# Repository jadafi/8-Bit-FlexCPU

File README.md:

# 8-Bit-FlexCPU
Building Blocks for an 8-Bit CPU

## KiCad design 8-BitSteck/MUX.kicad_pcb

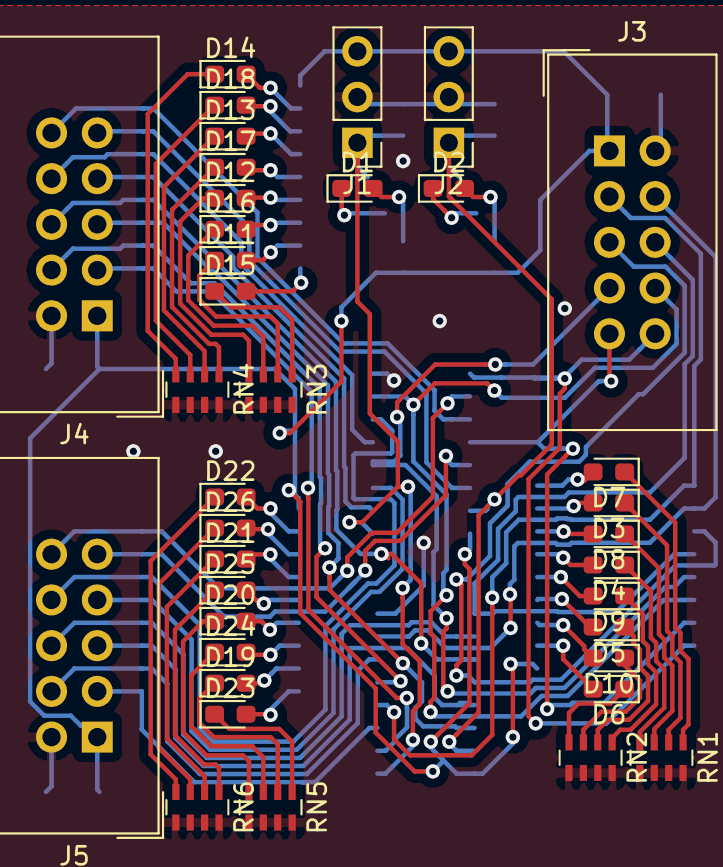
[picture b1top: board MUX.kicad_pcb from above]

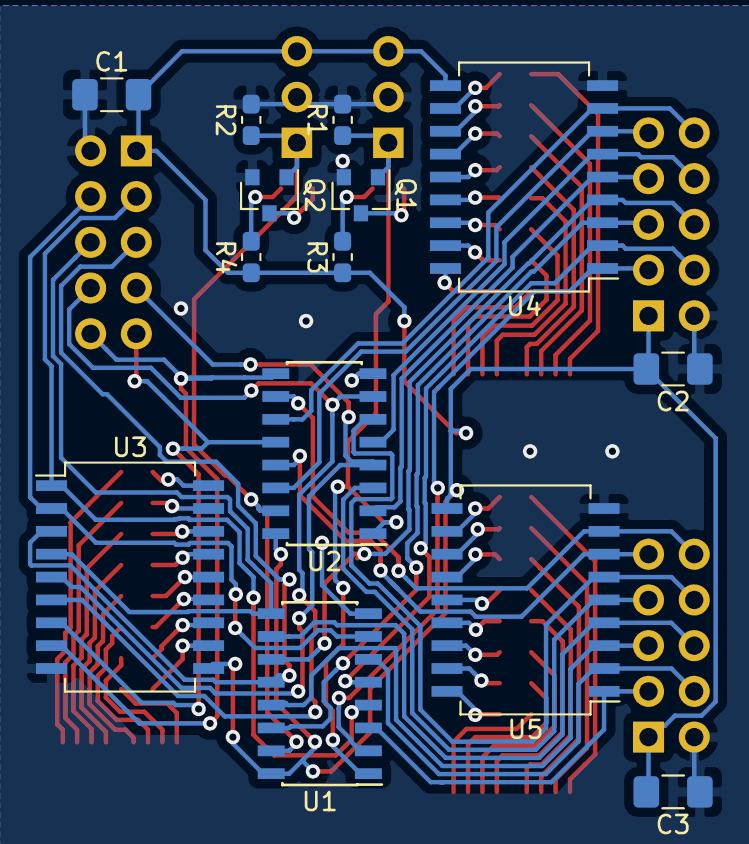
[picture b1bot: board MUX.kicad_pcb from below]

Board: 2 copper layers, 51 parts (14 on the bottom side), 80 nets.

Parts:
C1, C2, C3: _Decoupling; C_1206_3216Metric_Pad1.42x1.75mm_HandSolder
D1, D2: LED_Y; LED_0603_1608Metric_Pad1.05x0.95mm_HandSolder
D3, D4, D5, D6, D7, D8, D9, D10, D11, D12, D13, D14, D15, D16, D17, D18, D19, D20, D21, D22, D23, D24, D25, D26: LED; LED_0603_1608Metric_Pad1.05x0.95mm_HandSolder
J1, J2: Conn_01x03_Male; PinHeader_1x03_P2.54mm_Vertical
J3, J4, J5: Conn_02x05_Odd_Even; IDC-Header_2x05_P2.54mm_Vertical
Q1, Q2: 2N7002; SOT-23
R1, R2: R_default; R_0603_1608Metric_Pad1.05x0.95mm_HandSolder
R3, R4: R_Yellow; R_0603_1608Metric_Pad1.05x0.95mm_HandSolder
RN1, RN2, RN3, RN4, RN5, RN6: R_Pack04; R_Array_Concave_4x0603
U1, U2: 74LS157; SOIC-16_3.9x9.9mm_P1.27mm
U3, U4, U5: ULN2803A; SOP-18_7.0x12.5mm_P1.27mm

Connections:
+3V3: C1.2, C2.2, C3.2, J1.3, J2.3, J3.1, J4.1, J5.1, R3.1, R4.1, U1.16, U2.16, U3.10, U4.10, U5.10
/S: J1.1, Q1.1, R1.1, U1.1, U2.1
/a0: J4.3, U1.2, U4.1
/a1: J4.4, U1.5, U4.2
/a2: J4.5, U1.14, U4.3
/a3: J4.6, U1.11, U4.4
/a4: J4.7, U2.2, U4.5
/a5: J4.8, U2.5, U4.6
/a6: J4.9, U2.14, U4.7
/a7: J4.10, U2.11, U4.8
/b0: J5.3, U1.3, U5.1
/b1: J5.4, U1.6, U5.2
/b2: J5.5, U1.13, U5.3
/b3: J5.6, U1.10, U5.4
/b4: J5.7, U2.3, U5.5
/b5: J5.8, U2.6, U5.6
/b6: J5.9, U2.13, U5.7
/b7: J5.10, U2.10, U5.8
/out0: J3.3, U1.4, U3.1
/out1: J3.4, U1.7, U3.2
/out2: J3.5, U1.12, U3.3
/out3: J3.6, U1.9, U3.4
/out4: J3.7, U2.4, U3.5
/out5: J3.8, U2.7, U3.6
/out6: J3.9, U2.12, U3.7
/out7: J3.10, U2.9, U3.8
/~E: J2.1, Q2.1, R2.1, U1.15, U2.15
GND: C1.1, C2.1, C3.1, J1.2, J2.2, J3.2, J4.2, J5.2, Q1.2, Q2.2, R1.2, R2.2, RN1.5, RN1.6, RN1.7, RN1.8, RN2.5, RN2.6, RN2.7, RN2.8, RN3.5, RN3.6, RN3.7, RN3.8, RN4.5, RN4.6, RN4.7, RN4.8, RN5.5, RN5.6, RN5.7, RN5.8, RN6.5, RN6.6, RN6.7, RN6.8, U1.8, U2.8, U3.9, U4.9, U5.9
unnamed: D1.1, Q1.3
unnamed: D1.2, R3.2
unnamed: D2.1, Q2.3
unnamed: D2.2, R4.2
unnamed: D3.1, RN1.2
unnamed: D3.2, U3.17
unnamed: D4.1, RN1.4
unnamed: D4.2, U3.15
unnamed: D5.1, RN2.2
unnamed: D5.2, U3.13
unnamed: D6.1, RN2.4
unnamed: D6.2, U3.11
unnamed: D7.1, RN1.1
unnamed: D7.2, U3.18
unnamed: D8.1, RN1.3
unnamed: D8.2, U3.16
unnamed: D9.1, RN2.1
unnamed: D9.2, U3.14
unnamed: D10.1, RN2.3
unnamed: D10.2, U3.12
unnamed: D11.1, RN3.2
unnamed: D11.2, U4.17
unnamed: D12.1, RN3.4
unnamed: D12.2, U4.15
unnamed: D13.1, RN4.2
unnamed: D13.2, U4.13
unnamed: D14.1, RN4.4
unnamed: D14.2, U4.11
unnamed: D15.1, RN3.1
unnamed: D15.2, U4.18
unnamed: D16.1, RN3.3
unnamed: D16.2, U4.16
unnamed: D17.1, RN4.1
unnamed: D17.2, U4.14
unnamed: D18.1, RN4.3
unnamed: D18.2, U4.12
unnamed: D19.1, RN5.2
unnamed: D19.2, U5.17
unnamed: D20.1, RN5.4
unnamed: D20.2, U5.15
unnamed: D21.1, RN6.2
unnamed: D21.2, U5.13
unnamed: D22.1, RN6.4
unnamed: D22.2, U5.11
unnamed: D23.1, RN5.1
unnamed: D23.2, U5.18
unnamed: D24.1, RN5.3
unnamed: D24.2, U5.16
unnamed: D25.1, RN6.1
unnamed: D25.2, U5.14
unnamed: D26.1, RN6.3
unnamed: D26.2, U5.12

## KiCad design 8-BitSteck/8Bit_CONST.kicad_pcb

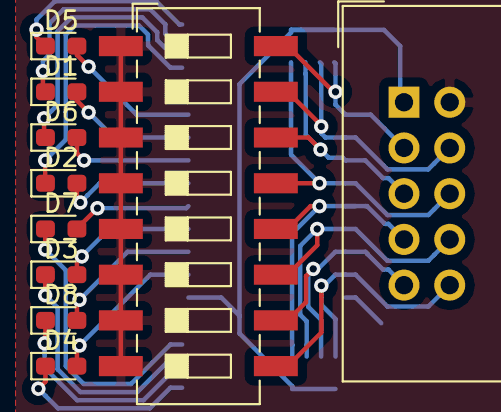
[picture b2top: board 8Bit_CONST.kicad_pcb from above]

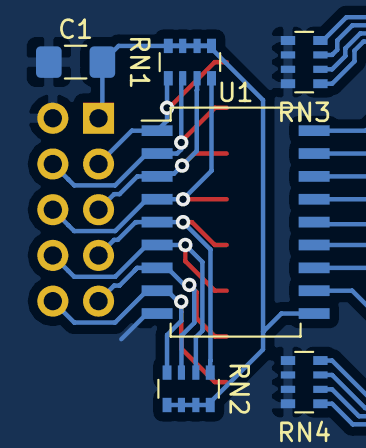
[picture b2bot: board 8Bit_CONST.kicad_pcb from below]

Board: 2 copper layers, 16 parts (6 on the bottom side), 26 nets.

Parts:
C1: _Decoupling; C_1206_3216Metric_Pad1.42x1.75mm_HandSolder
D1, D2, D3, D4, D5, D6, D7, D8: LED; LED_0603_1608Metric_Pad1.05x0.95mm_HandSolder
J1: Conn_02x05_Odd_Even; IDC-Header_2x05_P2.54mm_Vertical
RN1, RN2, RN3, RN4: R_Pack04; R_Array_Convex_4x0603
SW1: SW_DIP_x08; SW_DIP_SPSTx08_Slide_6.7x21.88mm_W8.61mm_P2.54mm_LowProfile
U1: ULN2803A; SOP-18_7.0x12.5mm_P1.27mm

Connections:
+3V3: C1.2, J1.1, RN1.5, RN1.6, RN1.7, RN1.8, RN2.5, RN2.6, RN2.7, RN2.8, U1.10
/bus0: J1.3, RN1.1, SW1.16, U1.1
/bus1: J1.4, RN1.2, SW1.15, U1.2
/bus2: J1.5, RN1.3, SW1.14, U1.3
/bus3: J1.6, RN1.4, SW1.13, U1.4
/bus4: J1.7, RN2.1, SW1.12, U1.5
/bus5: J1.8, RN2.2, SW1.11, U1.6
/bus6: J1.9, RN2.3, SW1.10, U1.7
/bus7: J1.10, RN2.4, SW1.9, U1.8
GND: C1.1, J1.2, RN3.5, RN3.6, RN3.7, RN3.8, RN4.5, RN4.6, RN4.7, RN4.8, SW1.1, SW1.2, SW1.3, SW1.4, SW1.5, SW1.6, SW1.7, SW1.8, U1.9
unnamed: D1.1, RN3.3
unnamed: D1.2, U1.17
unnamed: D2.1, RN3.1
unnamed: D2.2, U1.15
unnamed: D3.1, RN4.3
unnamed: D3.2, U1.13
unnamed: D4.1, RN4.1
unnamed: D4.2, U1.11
unnamed: D5.1, RN3.4
unnamed: D5.2, U1.18
unnamed: D6.1, RN3.2
unnamed: D6.2, U1.16
unnamed: D7.1, RN4.4
unnamed: D7.2, U1.14
unnamed: D8.1, RN4.2
unnamed: D8.2, U1.12

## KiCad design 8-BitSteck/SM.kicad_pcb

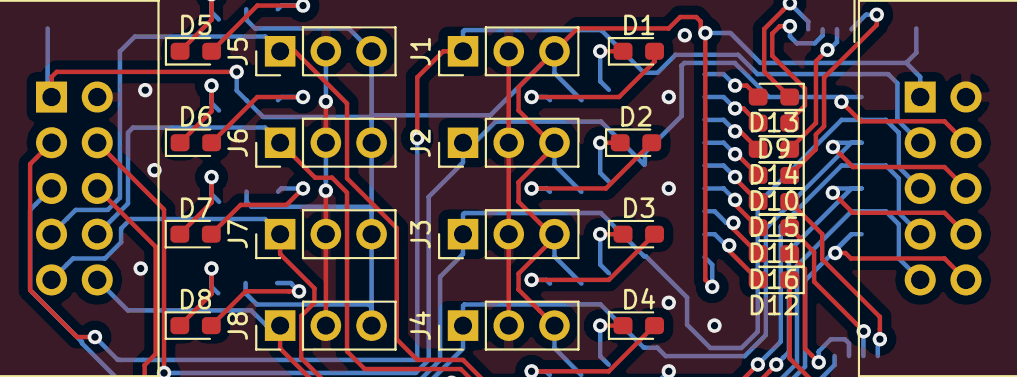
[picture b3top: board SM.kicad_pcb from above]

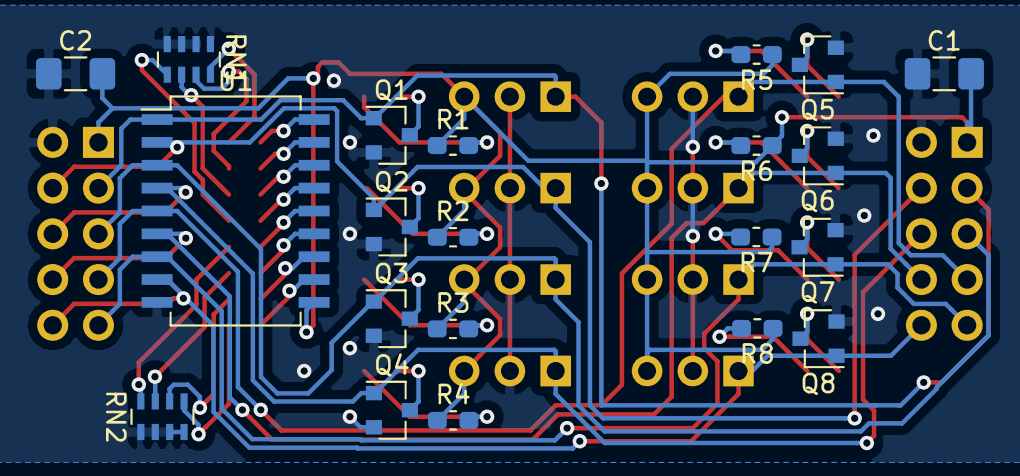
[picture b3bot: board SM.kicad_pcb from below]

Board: 2 copper layers, 47 parts (21 on the bottom side), 42 nets.

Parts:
C1, C2: _Decoupling; C_1206_3216Metric_Pad1.42x1.75mm_HandSolder
D1, D2, D3, D4, D5, D6, D7, D8: LED_Y; LED_0603_1608Metric_Pad1.05x0.95mm_HandSolder
D9, D10, D11, D12, D13, D14, D15, D16: LED; LED_0603_1608Metric_Pad1.05x0.95mm_HandSolder
J1, J2, J3, J4, J5, J6, J7, J8: Conn_01x03_Male; PinHeader_1x03_P2.54mm_Vertical
J9, J10: Conn_02x05_Odd_Even; IDC-Header_2x05_P2.54mm_Vertical
Q1, Q2, Q3, Q4, Q5, Q6, Q7, Q8: 2N7002; SOT-23
R1, R2, R3, R4, R5, R6, R7, R8: R_Yellow; R_0603_1608Metric_Pad1.05x0.95mm_HandSolder
RN1, RN2: R_Pack04; R_Array_Concave_4x0603
U1: ULN2803A; SOP-18_7.0x12.5mm_P1.27mm

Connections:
+3V3: C1.2, C2.2, J1.3, J2.3, J3.3, J4.3, J5.3, J6.3, J7.3, J8.3, J9.1, J10.1, R1.1, R2.1, R3.1, R4.1, R5.1, R6.1, R7.1, R8.1, U1.10
/bus_0: J1.1, J9.3, J10.3, Q1.1, U1.1
/bus_1: J2.1, J9.4, J10.4, Q2.1, U1.2
/bus_2: J3.1, J9.5, J10.5, Q3.1, U1.3
/bus_3: J4.1, J9.6, J10.6, Q4.1, U1.4
/bus_4: J5.1, J9.7, J10.7, Q5.1, U1.5
/bus_5: J6.1, J9.8, J10.8, Q6.1, U1.6
/bus_6: J7.1, J9.9, J10.9, Q7.1, U1.7
/bus_7: J8.1, J9.10, J10.10, Q8.1, U1.8
GND: C1.1, C2.1, J1.2, J2.2, J3.2, J4.2, J5.2, J6.2, J7.2, J8.2, J9.2, J10.2, Q1.2, Q2.2, Q3.2, Q4.2, Q5.2, Q6.2, Q7.2, Q8.2, RN1.1, RN1.2, RN1.3, RN1.4, RN2.1, RN2.2, RN2.3, RN2.4, U1.9
unnamed: D1.1, Q1.3
unnamed: D1.2, R1.2
unnamed: D2.1, Q2.3
unnamed: D2.2, R2.2
unnamed: D3.1, Q3.3
unnamed: D3.2, R3.2
unnamed: D4.1, Q4.3
unnamed: D4.2, R4.2
unnamed: D5.1, Q5.3
unnamed: D5.2, R5.2
unnamed: D6.1, Q6.3
unnamed: D6.2, R6.2
unnamed: D7.1, Q7.3
unnamed: D7.2, R7.2
unnamed: D8.1, Q8.3
unnamed: D8.2, R8.2
unnamed: D9.1, RN1.7
unnamed: D9.2, U1.17
unnamed: D10.1, RN1.5
unnamed: D10.2, U1.15
unnamed: D11.1, RN2.7
unnamed: D11.2, U1.13
unnamed: D12.1, RN2.5
unnamed: D12.2, U1.11
unnamed: D13.1, RN1.8
unnamed: D13.2, U1.18
unnamed: D14.1, RN1.6
unnamed: D14.2, U1.16
unnamed: D15.1, RN2.8
unnamed: D15.2, U1.14
unnamed: D16.1, RN2.6
unnamed: D16.2, U1.12

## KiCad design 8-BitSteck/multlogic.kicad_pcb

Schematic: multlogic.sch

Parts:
R1, R2, R3, R4: R; R_0603_1608Metric_Pad1.05x0.95mm_HandSolder
RN2, RN3: R_Pack04; R_Array_Convex_4x0603
U1: 74HC00; SOIC-14_3.9x8.7mm_P1.27mm
U2: 74HC02; SOIC-14_3.9x8.7mm_P1.27mm

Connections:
+3V3: R1.1, R2.1, RN2.5, RN2.6, RN2.7, RN2.8, U1.14 (VCC), U2.14 (VCC); also elsewhere on the board
/AND_A: RN2.1, U1.1; also elsewhere on the board
/AND_B: RN2.2, U1.2; also elsewhere on the board
/AND_C: RN2.3, U1.12; also elsewhere on the board
/AND_D: RN2.4, U1.13; also elsewhere on the board
/AND_Q: U2.13; also elsewhere on the board
/NAND_A: R2.2, U1.9; also elsewhere on the board
/NAND_B: R1.2, U1.10; also elsewhere on the board
/NAND_Q: U1.8; also elsewhere on the board
/NOR_A: R3.1, U2.3; also elsewhere on the board
/NOR_B: R4.1, U2.2; also elsewhere on the board
/NOR_Q: U2.1; also elsewhere on the board
/OR_A: RN3.7, U2.5; also elsewhere on the board
/OR_B: RN3.8, U2.6; also elsewhere on the board
/OR_C: RN3.6, U2.9; also elsewhere on the board
/OR_D: RN3.5, U2.8; also elsewhere on the board
/OR_Q: U1.6; also elsewhere on the board
GND: R3.2, R4.2, RN3.1, RN3.2, RN3.3, RN3.4, U1.7 (GND), U2.7 (GND); also elsewhere on the board
unnamed: U1.3, U2.11
unnamed: U1.4, U2.4
unnamed: U1.5, U2.10
unnamed: U1.11, U2.12

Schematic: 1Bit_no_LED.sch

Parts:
J1: Conn_01x03_Male; PinHeader_1x03_P2.54mm_Vertical

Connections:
+3V3: J1.3; also elsewhere on the board
/AND_A: J1.1; also elsewhere on the board
GND: J1.2; also elsewhere on the board

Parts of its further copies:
J2, J3, J4, J5, J6, J7, J8, J9, J10, J11, J12, J13, J14, J15, J16: Conn_01x03_Male; PinHeader_1x03_P2.54mm_Vertical

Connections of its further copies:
+3V3: J2.3, J3.3, J4.3, J5.3, J6.3, J7.3, J8.3, J9.3, J10.3, J11.3, J12.3, J13.3, J14.3, J15.3, J16.3; also elsewhere on the board
/AND_B: J2.1; also elsewhere on the board
/AND_C: J3.1; also elsewhere on the board
/AND_D: J4.1; also elsewhere on the board
/AND_Q: J13.1; also elsewhere on the board
/NAND_A: J9.1; also elsewhere on the board
/NAND_B: J10.1; also elsewhere on the board
/NAND_Q: J15.1; also elsewhere on the board
/NOR_A: J11.1; also elsewhere on the board
/NOR_B: J12.1; also elsewhere on the board
/NOR_Q: J16.1; also elsewhere on the board
/OR_A: J5.1; also elsewhere on the board
/OR_B: J6.1; also elsewhere on the board
/OR_C: J7.1; also elsewhere on the board
/OR_D: J8.1; also elsewhere on the board
/OR_Q: J14.1; also elsewhere on the board
GND: J2.2, J3.2, J4.2, J5.2, J6.2, J7.2, J8.2, J9.2, J10.2, J11.2, J12.2, J13.2, J14.2, J15.2, J16.2; also elsewhere on the board

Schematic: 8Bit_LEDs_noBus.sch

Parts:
D1, D2, D3, D4, D5, D6, D7, D8: LED; LED_0603_1608Metric_Pad1.05x0.95mm_HandSolder
RN4, RN5: R_Pack04; R_Array_Convex_4x0603
U3: ULN2803A; SOP-18_7.0x12.5mm_P1.27mm

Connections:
+3V3: U3.10; also elsewhere on the board
/AND_A: U3.1; also elsewhere on the board
/AND_B: U3.2; also elsewhere on the board
/AND_C: U3.4; also elsewhere on the board
/AND_D: U3.3; also elsewhere on the board
/AND_Q: U3.8; also elsewhere on the board
/NAND_A: U3.6; also elsewhere on the board
/NAND_B: U3.5; also elsewhere on the board
/NAND_Q: U3.7; also elsewhere on the board
GND: RN4.1, RN4.2, RN4.3, RN4.4, RN5.1, RN5.2, RN5.3, RN5.4, U3.9; also elsewhere on the board
unnamed: D1.1, RN4.7
unnamed: D1.2, U3.17
unnamed: D2.1, RN4.5
unnamed: D2.2, U3.15
unnamed: D3.1, RN5.7
unnamed: D3.2, U3.13
unnamed: D4.1, RN5.5
unnamed: D4.2, U3.11
unnamed: D5.1, RN4.8
unnamed: D5.2, U3.18
unnamed: D6.1, RN4.6
unnamed: D6.2, U3.16
unnamed: D7.1, RN5.8
unnamed: D7.2, U3.14
unnamed: D8.1, RN5.6
unnamed: D8.2, U3.12

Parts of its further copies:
D9, D10, D11, D12, D13, D14, D15, D16: LED; LED_0603_1608Metric_Pad1.05x0.95mm_HandSolder
RN6, RN7: R_Pack04; R_Array_Convex_4x0603
U4: ULN2803A; SOP-18_7.0x12.5mm_P1.27mm

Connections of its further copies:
+3V3: U4.10; also elsewhere on the board
/NOR_A: U4.6; also elsewhere on the board
/NOR_B: U4.7; also elsewhere on the board
/NOR_Q: U4.8; also elsewhere on the board
/OR_A: U4.5; also elsewhere on the board
/OR_B: U4.4; also elsewhere on the board
/OR_C: U4.2; also elsewhere on the board
/OR_D: U4.3; also elsewhere on the board
/OR_Q: U4.1; also elsewhere on the board
GND: RN6.1, RN6.2, RN6.3, RN6.4, RN7.1, RN7.2, RN7.3, RN7.4, U4.9; also elsewhere on the board
unnamed: D9.1, RN6.7
unnamed: D9.2, U4.17
unnamed: D10.1, RN6.5
unnamed: D10.2, U4.15
unnamed: D11.1, RN7.7
unnamed: D11.2, U4.13
unnamed: D12.1, RN7.5
unnamed: D12.2, U4.11
unnamed: D13.1, RN6.8
unnamed: D13.2, U4.18
unnamed: D14.1, RN6.6
unnamed: D14.2, U4.16
unnamed: D15.1, RN7.8
unnamed: D15.2, U4.14
unnamed: D16.1, RN7.6
unnamed: D16.2, U4.12

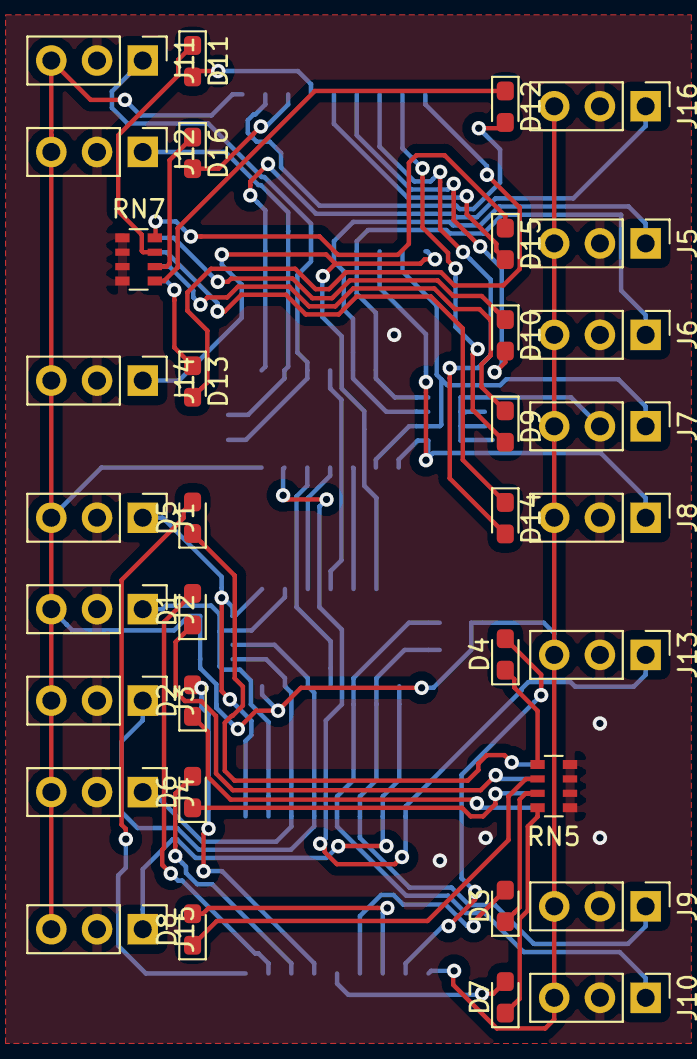
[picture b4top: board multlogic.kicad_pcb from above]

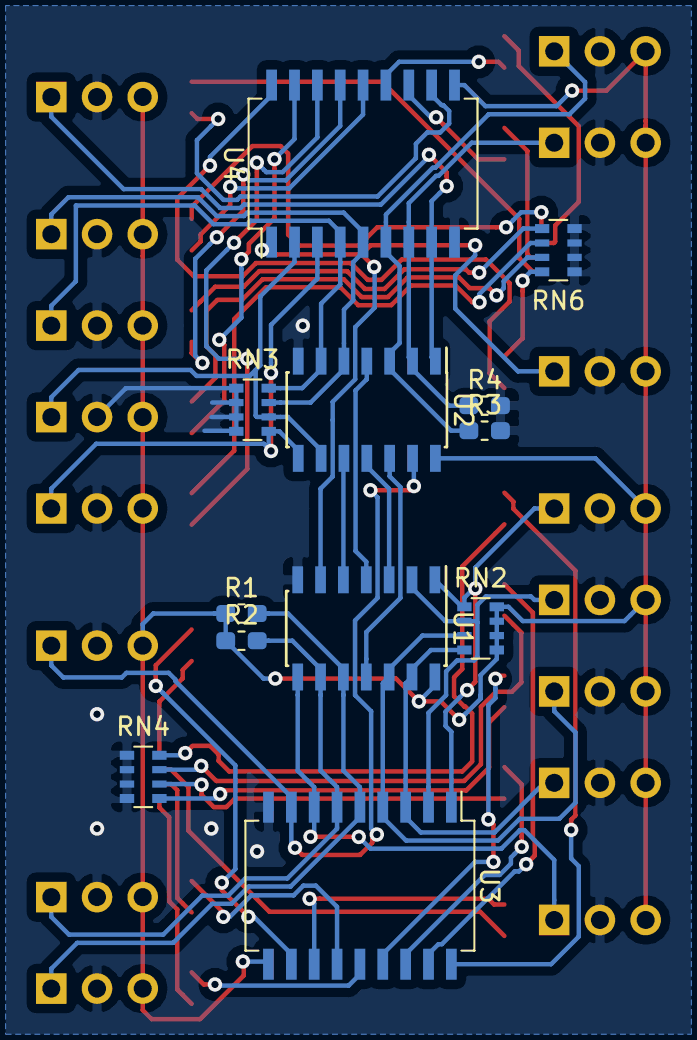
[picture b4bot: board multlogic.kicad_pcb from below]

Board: 2 copper layers, 46 parts (12 on the bottom side), 54 nets.

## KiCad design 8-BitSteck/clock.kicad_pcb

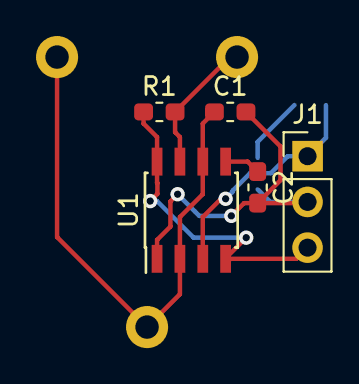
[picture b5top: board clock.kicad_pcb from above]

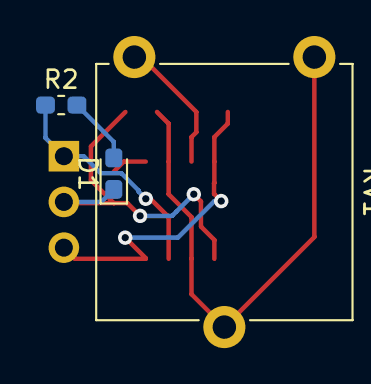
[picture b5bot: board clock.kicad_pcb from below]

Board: 2 copper layers, 8 parts (3 on the bottom side), 7 nets.

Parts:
C1, C2: 0.01uF; C_0603_1608Metric_Pad1.05x0.95mm_HandSolder
D1: LED_BLUE; LED_0603_1608Metric_Pad1.05x0.95mm_HandSolder
J1: Conn_01x03_Male; PinHeader_1x03_P2.54mm_Vertical
R1: 1K; R_0603_1608Metric_Pad1.05x0.95mm_HandSolder
R2: 80; R_0603_1608Metric_Pad1.05x0.95mm_HandSolder
RV1: 1M; Potentiometer_ACP_CA14V-15_Vertical
U1: NE555; SOIC-8_3.9x4.9mm_P1.27mm

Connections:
+3V3: J1.3, R1.1, U1.4, U1.8
/clock/Clock: J1.1, R2.1, U1.3
GND: C1.2, C2.2, D1.1, J1.2, U1.1
unnamed: C1.1, RV1.2, RV1.3, U1.2, U1.6
unnamed: C2.1, U1.5
unnamed: D1.2, R2.2
unnamed: R1.2, RV1.1, U1.7

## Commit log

2018-11-16 Multilogic routed
2018-11-16 8-bit-Const routed
